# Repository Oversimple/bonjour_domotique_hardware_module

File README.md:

bonjour_domotique_hardware_module
=================================

The eagle project for bonjour domotique

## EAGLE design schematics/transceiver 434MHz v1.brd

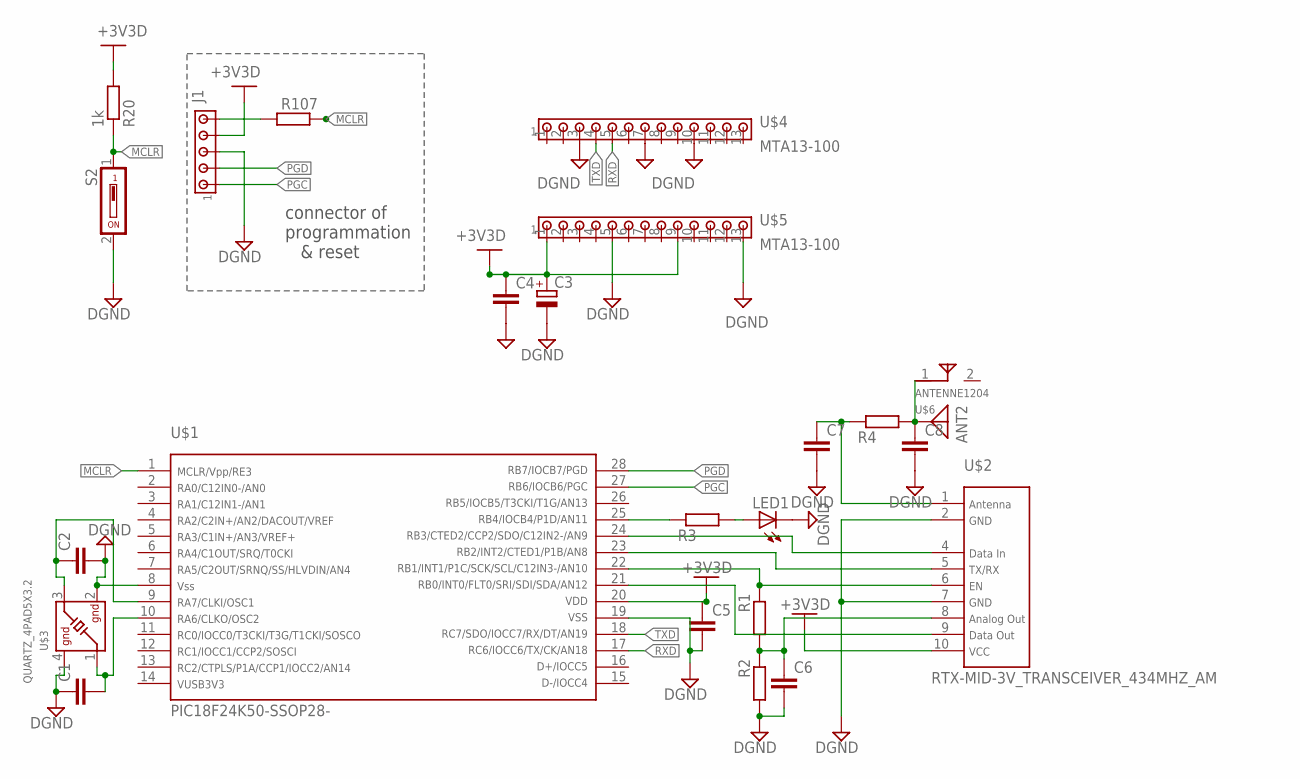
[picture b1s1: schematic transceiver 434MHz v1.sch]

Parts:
ANT2: ANTENNA; PAD-01
C1, C2, C4, C5, C6, C7, C8: C-EUC0805; C0805
C3: CPOL-EUSMCB; SMC_B
J1: MTA05-100; 10X05MTA
LED1: LEDCHIPLED_0805; CHIPLED_0805
R1, R2, R3, R4, R107: R-EU_R0805; R0805
R20: 1k; R0805
S2: DS01; DS-01
U$1: PIC18F24K50-SSOP28-; SOP254P785X200-28N
U$2: RTX-MID-3V_TRANSCEIVER_434MHZ_AM; TRASCEIVER-434MHZ_AM
U$3: QUARTZ_4PAD5X3.2; OSC_5X3.2
U$4, U$5: MTA13-100; 10X13MTA
U$6: ANTENNE1204

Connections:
+3V3D: C3.+, C4.1, C5.1, J1.4, R20.2, U$1.20, U$2.10, U$5.1, U$5.9
DGND: C1.1, C2.2, C3.-, C4.2, C5.2, C6.2, C7.2, C8.2, J1.3, LED1.C, R2.2, S2.2, U$1.8, U$1.19, U$2.2, U$2.7, U$3.2, U$3.4, U$4.3, U$4.7, U$4.10, U$5.5, U$5.13
MCLR: R20.1, R107.1, S2.1, U$1.1
unnamed: U$1.21, U$2.9
unnamed: C6.1, R1.2, R2.1, U$2.8
unnamed: R1.1, U$1.22, U$2.6
unnamed: U$1.23, U$2.5
unnamed: U$1.24, U$2.4
unnamed: C7.1, R4.1, U$2.1
unnamed: R3.1, U$1.25
unnamed: LED1.A, R3.2
unnamed: C1.2, U$1.10, U$3.1
unnamed: C2.1, U$1.9, U$3.3
unnamed: ANT2.1, C8.1, R4.2, U$6.1
unnamed: J1.5, R107.2
PGC: J1.1, U$1.27
PGD: J1.2, U$1.28
RXD: U$1.17, U$4.5
TXD: U$1.18, U$4.4

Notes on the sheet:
connector of programmation & reset

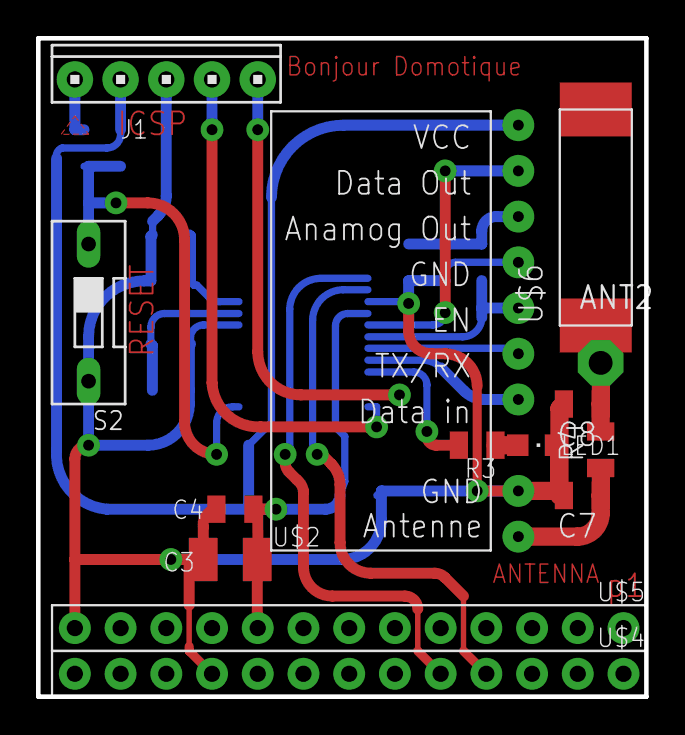
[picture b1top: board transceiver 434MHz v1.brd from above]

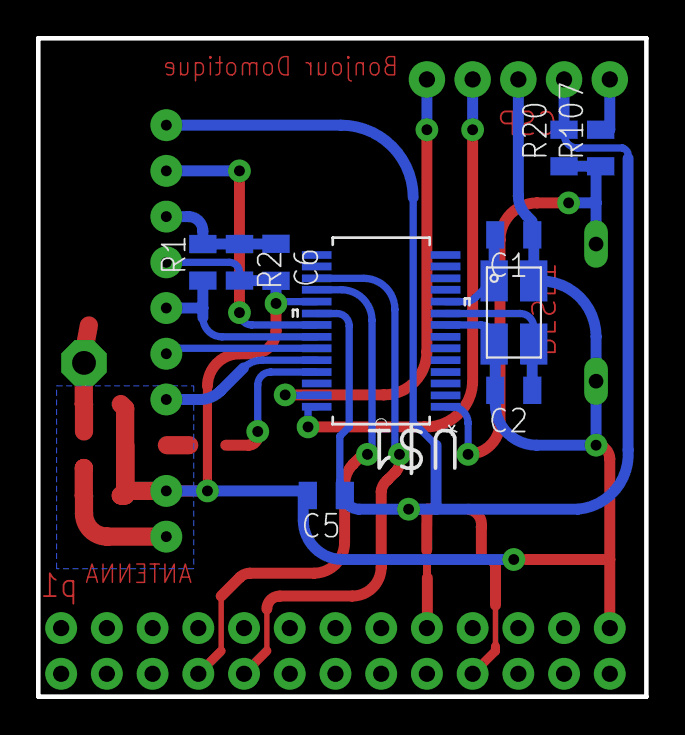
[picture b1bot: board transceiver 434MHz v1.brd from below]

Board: 2 copper layers, 33.8 x 36.6 mm, 24 parts (10 on the bottom side), 19 nets.

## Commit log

2014-12-17 Adding the schematics for the hardwre module
2014-12-17 Adding the mplabx project
2014-12-21 Adding the php and C modules
2014-12-21 adding C sources

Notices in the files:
parts and their libraries:
supply0: Copyright (C) 2007, Bob Starr
